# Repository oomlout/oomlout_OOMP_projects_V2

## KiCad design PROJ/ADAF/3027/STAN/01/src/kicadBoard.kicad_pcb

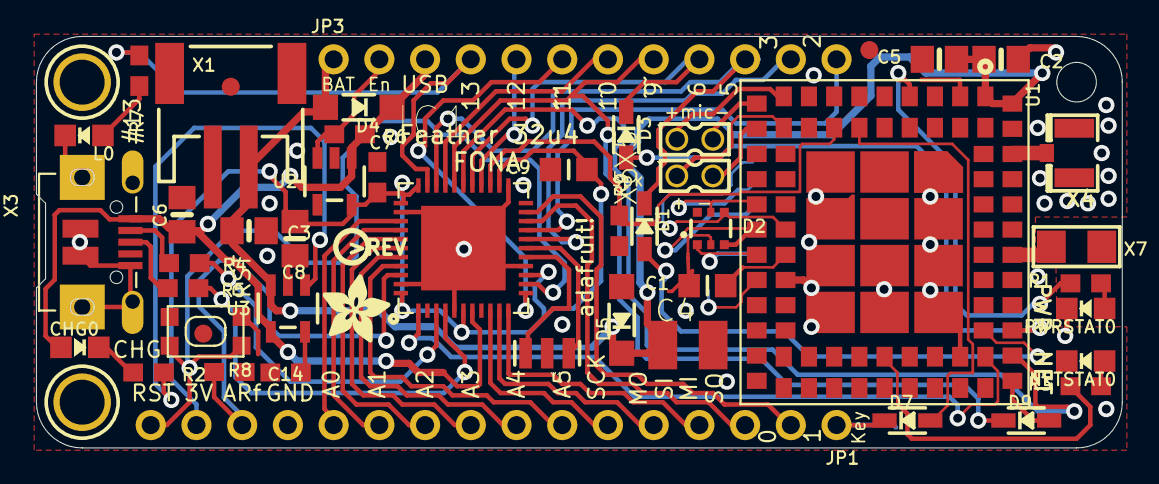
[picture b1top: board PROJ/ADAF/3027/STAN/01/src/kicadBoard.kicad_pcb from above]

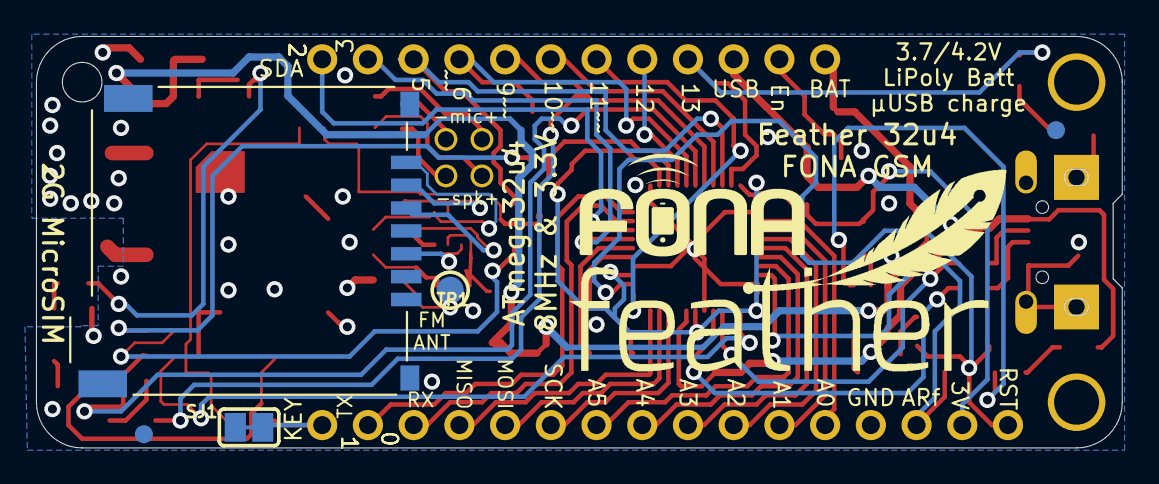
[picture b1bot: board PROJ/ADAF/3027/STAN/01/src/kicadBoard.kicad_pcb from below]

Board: 2 copper layers, 60.3 x 22.9 mm, 59 parts (7 on the bottom side), 61 nets.

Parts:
@HOLE0: (no value)
C1, C9: 10uF; _0805MP
C2: 33pF; 0805-NO
C3, C6, C8: 10µF; 0805-NO
C4: 100uF; C1210
C5: 10pF; 0805-NO
C7, C14: 1uF; 0603-NO
CHG0: ORANGE; CHIPLED_0805_NOOUTLINE
D1, D3, D7, D9: 1N4148; SOD-323
D2: SMF05C; SOT363
D4: MBR120; SOD-123
D5: MMSZ5231BT1G; SOD-123
IC1: ATMEGA32U4-MU; TQFN44_7MM
JP1: 1X16_ROUND
JP3: 1X12_ROUND
L0: RED; CHIPLED_0805_NOOUTLINE
NETSTAT0: BLUE; CHIPLED_0805_NOOUTLINE
PWRSTAT0: GREEN; CHIPLED_0805_NOOUTLINE
R1, R2, R3: 1K; 0603-NO
R4, R5: 22; 0603-NO
R6: 100k; 0603-NO
R7, R8: 2.2K; 0603-NO
R9: DNP; 0603-NO
SJ1: SOLDERJUMPER_CLOSEDWIRE
SW1: SPST_TACT-KMR2; KMR2
TP1: TESTPOINT_ROUND_1.5MM
U1: SIM800H/L; SIM800L
U2: AP2112-3.3K; SOT23-5
U3: MCP73831T-2ACI/OT; SOT23-5
U$7: ADAFRUIT_3.5MM
U$18, U$23, U$34, U$35, U$42: FIDUCIAL""; FIDUCIAL_1MM
U$25: FEATHERLOGO
U$31, U$32: MOUNTINGHOLE2.5; MOUNTINGHOLE_2.5_PLATED
U$43: FONA_LOGO_SMALL
U$44: PCBFEAT-REV-040
X1: JSTPH; JSTPH2
X2: 4UCON 20217; 4UCONN_20217
X3: microUSB; 4UCONN_20329_V2
X4: uFL; U.FL
X5, X6: 1x2; 87758-0216
X7: ANT_2450AT18B100
Y1: 8MHz; RESONATOR-SMD

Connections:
0: IC1.20, JP1.3
1: IC1.21, JP1.2
1.8V: D2.1, U1.16, X2.VCC
2: IC1.19, JP3.12
3: IC1.18, JP3.11
4_RST: IC1.25, R9.2, U1.49
5_UART_DTR: D1.C, IC1.31, JP3.10
6_UART_RTS: D3.C, IC1.27, JP3.9
7_UART_RI: IC1.1, U1.68
8_UART_TXD: IC1.28, U1.32
9_UART_RXD: D9.C, IC1.29, JP3.8
10: IC1.30, JP3.7
11: IC1.12, JP3.6
12: IC1.26, JP3.5
13: IC1.32, JP3.4, R7.1
+3V3: C7.1, C8.1, C9.1, IC1.6, IC1.14, IC1.24, IC1.33, IC1.34, IC1.44, JP1.15, U2.5
A0: IC1.36, JP1.12
A1: IC1.37, JP1.11
A2: IC1.38, JP1.10
A3: IC1.39, JP1.9
A4: IC1.40, JP1.8
A5: IC1.41, JP1.7
AREF: C14.1, IC1.42, JP1.14
D+: IC1.4, R5.2
D-: IC1.3, R4.2
EN: JP3.2, R6.1, U2.3
FM_ANT: TP1.P$1, U1.17
GND: C1.2, C2.2, C3.2, C4.2, C5.2, C6.2, C7.2, C8.2, C9.2, C14.2, D2.2, D5.A, IC1.5, IC1.15, IC1.23, IC1.35, IC1.43, JP1.13, L0.C, NETSTAT0.C, PWRSTAT0.C, R8.2, R9.1, SJ1.1, SW1.2, SW1.4, U1.2, U1.6, U1.8, U1.35, U1.37, U1.38, U1.39, U1.41, U1.43, U1.44, U1.45, U1.57, U1.58, U1.67, U1.71, U1.72, U1.73, U1.76, U1.77, U1.78, U1.79, U1.80, U1.81, U1.82, U1.83, U1.84, U1.85, U1.86, U1.87, U1.88, U2.2, U3.2, X1.1, X2.GND, X2.GND@1, X2.GND@2, X2.GND@3, X2.GND@4, X3.BASE@1, X3.BASE@2, X3.GND, X3.SPRT@1, X3.SPRT@2, X3.SPRT@3, X3.SPRT@4, X4.1, X4.2, Y1.2
GSM_ANT: U1.40, X4.3
KEY: D7.C, JP1.1, SJ1.2
MIC2+: U1.9, X5.1
MIC2-: U1.10, X5.2
MISO: IC1.11, JP1.4
MOSI: IC1.10, JP1.5
unnamed: CHG0.C, R2.1
unnamed: L0.A, R7.2
unnamed: R2.2, U3.1
unnamed: R8.1, U3.5
unnamed: PWRSTAT0.A, R1.1
unnamed: U1.36, X7.FP
unnamed: D7.A, U1.48
unnamed: NETSTAT0.A, R3.1
unnamed: IC1.16, Y1.3
unnamed: IC1.17, Y1.1
unnamed: R5.1, X3.D+
unnamed: R4.1, X3.D-
NETSTAT: R3.2, U1.64
PWRSTAT: R1.2, U1.4
RST: IC1.13, JP1.16, SW1.1, SW1.3
SCK: IC1.9, JP1.6
SIMCLK: D2.4, U1.55, X2.CLK
SIMDATA: D2.5, U1.14, X2.I/O
SIMRST: D2.3, U1.15, X2.RST
SPEAKER2+: U1.51, X6.1
SPEAKER2-: U1.11, X6.2
UART_DTR: D1.A, U1.69
UART_RTS: D3.A, U1.33
UART_RXD: D9.A, U1.31
VBAT: C2.1, C3.1, C4.1, C5.1, D4.A, D5.C, JP3.1, U1.1, U1.42, U3.3, X1.2
VBUS: C6.1, CHG0.A, D4.C, IC1.7, JP3.3, R6.2, U1.7, U2.1, U3.4, X3.VBUS
VRTC: C1.1, U1.56

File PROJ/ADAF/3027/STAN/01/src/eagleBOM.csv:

"Part";"Value";"Device";"Package";"Description";"BOM";"MF";"MPN";"OC_FARNELL";"OC_NEWARK";
"C1";"10uF";"CAP_CERAMIC_0805MP";"_0805MP";"Ceramic Capacitors";"";"";"";"";"";
"C2";"33pF";"CAP_CERAMIC0805-NOOUTLINE";"0805-NO";"Ceramic Capacitors";"";"";"";"";"";
"C3";"10µF";"CAP_CERAMIC0805-NOOUTLINE";"0805-NO";"Ceramic Capacitors";"";"";"";"";"";
"C4";"100uF";"C-USC1210";"C1210";"CAPACITOR, American symbol";"";"";"";"";"";
"C5";"10pF";"CAP_CERAMIC0805-NOOUTLINE";"0805-NO";"Ceramic Capacitors";"";"";"";"";"";
"C6";"10µF";"CAP_CERAMIC0805-NOOUTLINE";"0805-NO";"Ceramic Capacitors";"";"";"";"";"";
"C7";"1uF";"CAP_CERAMIC0603_NO";"0603-NO";"Ceramic Capacitors";"";"";"";"";"";
"C8";"10µF";"CAP_CERAMIC0805-NOOUTLINE";"0805-NO";"Ceramic Capacitors";"";"";"";"";"";
"C9";"10uF";"CAP_CERAMIC_0805MP";"_0805MP";"Ceramic Capacitors";"";"";"";"";"";
"C14";"1uF";"CAP_CERAMIC0603_NO";"0603-NO";"Ceramic Capacitors";"";"";"";"";"";
"CHG";"ORANGE";"LED0805_NOOUTLINE";"CHIPLED_0805_NOOUTLINE";"LED";"";"";"";"";"";
"D1";"1N4148";"DIODESOD-323";"SOD-323";"Diode";"";"";"";"";"";
"D2";"SMF05C";"TVSARRAY_5LANE";"SOT363";"Voltage Transient Suppressor Array";"";"";"";"";"";
"D3";"1N4148";"DIODESOD-323";"SOD-323";"Diode";"";"";"";"";"";
"D4";"MBR120";"DIODE-SCHOTTKYSOD-123";"SOD-123";"";"";"";"";"";"";
"D5";"MMSZ5231BT1G";"DIODE-ZENERSOD123";"SOD-123";"Zener Diode";"";"";"";"";"";
"D7";"1N4148";"DIODESOD-323";"SOD-323";"Diode";"";"";"";"";"";
"D9";"1N4148";"DIODESOD-323";"SOD-323";"Diode";"";"";"";"";"";
"IC1";"ATMEGA32U4-MU";"ATMEGA32U4-MU";"TQFN44_7MM";"http://www.ladyada.net/library/eagle";"";"";"";"";"";
"JP1";"";"HEADER-1X16ROUND";"1X16_ROUND";"PIN HEADER";"";"";"";"";"";
"JP3";"";"HEADER-1X12";"1X12_ROUND";"";"";"";"";"";"";
"L";"RED";"LED0805_NOOUTLINE";"CHIPLED_0805_NOOUTLINE";"LED";"";"";"";"";"";
"NETSTAT";"BLUE";"LED0805_NOOUTLINE";"CHIPLED_0805_NOOUTLINE";"LED";"";"";"";"";"";
"PWRSTAT";"GREEN";"LED0805_NOOUTLINE";"CHIPLED_0805_NOOUTLINE";"LED";"";"";"";"";"";
"R1";"1K";"RESISTOR_0603_NOOUT";"0603-NO";"Resistors";"";"";"";"";"";
"R2";"1K";"RESISTOR_0603_NOOUT";"0603-NO";"Resistors";"";"";"";"";"";
"R3";"1K";"RESISTOR_0603_NOOUT";"0603-NO";"Resistors";"";"";"";"";"";
"R4";"22";"RESISTOR_0603_NOOUT";"0603-NO";"Resistors";"";"";"";"";"";
"R5";"22";"RESISTOR_0603_NOOUT";"0603-NO";"Resistors";"";"";"";"";"";
"R6";"100k";"RESISTOR_0603_NOOUT";"0603-NO";"Resistors";"";"";"";"";"";
"R7";"2.2K";"RESISTOR_0603_NOOUT";"0603-NO";"Resistors";"";"";"";"";"";
"R8";"2.2K";"RESISTOR_0603_NOOUT";"0603-NO";"Resistors";"";"";"";"";"";
"R9";"DNP";"RESISTOR_0603_NOOUT";"0603-NO";"Resistors";"";"";"";"";"";
"SJ1";"";"SOLDERJUMPER_CLOSED";"SOLDERJUMPER_CLOSEDWIRE";"Solder Jumper - Closed";"";"";"";"";"";
"SW1";"SPST_TACT-KMR2";"SPST_TACT-KMR2";"KMR2";"SMT 6mm switch, EVQQ2 series";"";"";"";"";"";
"TP1";"";"TESTPOINTROUND1.5MM";"TESTPOINT_ROUND_1.5MM";"Test Point";"";"";"";"";"";
"U$18";"FIDUCIAL""";"FIDUCIAL""";"FIDUCIAL_1MM";"Fiducial Alignment Points";"EXCLUDE";"";"";"";"";
"U$23";"FIDUCIAL""";"FIDUCIAL""";"FIDUCIAL_1MM";"Fiducial Alignment Points";"EXCLUDE";"";"";"";"";
"U$31";"MOUNTINGHOLE2.5";"MOUNTINGHOLE2.5";"MOUNTINGHOLE_2.5_PLATED";"Mounting Hole";"EXCLUDE";"";"";"";"";
"U$32";"MOUNTINGHOLE2.5";"MOUNTINGHOLE2.5";"MOUNTINGHOLE_2.5_PLATED";"Mounting Hole";"EXCLUDE";"";"";"";"";
"U$34";"FIDUCIAL""";"FIDUCIAL""";"FIDUCIAL_1MM";"Fiducial Alignment Points";"EXCLUDE";"";"";"";"";
"U$35";"FIDUCIAL""";"FIDUCIAL""";"FIDUCIAL_1MM";"Fiducial Alignment Points";"EXCLUDE";"";"";"";"";
"U$42";"FIDUCIAL""";"FIDUCIAL""";"FIDUCIAL_1MM";"Fiducial Alignment Points";"EXCLUDE";"";"";"";"";
"U1";"SIM800H/L";"GSM_SIM800L";"SIM800L";"SIM800K Quad-Band GSM/GPRS Module";"";"";"";"";"";
"U2";"AP2112-3.3K";"VREG_SOT23-5";"SOT23-5";"SOT23-5 Fixed Voltage Regulators";"";"";"";"";"";
"U3";"MCP73831T-2ACI/OT";"MCP73831/2";"SOT23-5";"MCP73831/2 LIPO Charger";"";"";"";"";"";
"X1";"JSTPH";"CON_JST_PH_2PIN";"JSTPH2";"JST 2-Pin Right-Angle Connector";"";"";"";"";"";
"X2";"4UCON 20217";"SIM_MICRO";"4UCONN_20217";"Micro SIM Card Holder";"";"";"";"";"";
"X3";"microUSB";"USB_MICRO_20329_V2";"4UCONN_20329_V2";"USB Connectors";"";"";"";"";"";
"X4";"uFL";"ANTENNA_U.FL";"U.FL";"U.FL Antenna Connector";"";"";"";"";"";
"X5";"1x2";"87758-0216";"87758-0216";"2 Pin - 2mm Dual Row Single Wafer, Vertical T/H HDR";"";"";"87758-0216";"unknown";"94M1513";
"X6";"1x2";"87758-0216";"87758-0216";"2 Pin - 2mm Dual Row Single Wafer, Vertical T/H HDR";"";"";"87758-0216";"unknown";"94M1513";
"X7";"ANT_2450AT18B100";"ANTENNA_JOHANSON_2450AT18B100";"ANT_2450AT18B100";"Johanson 2.4GHz Chip Antenna (1206 Package)";"";"";"";"";"";
"Y1";"8MHz";"RESONATORSMD";"RESONATOR-SMD";"Resonator";"";"";"";"";"";

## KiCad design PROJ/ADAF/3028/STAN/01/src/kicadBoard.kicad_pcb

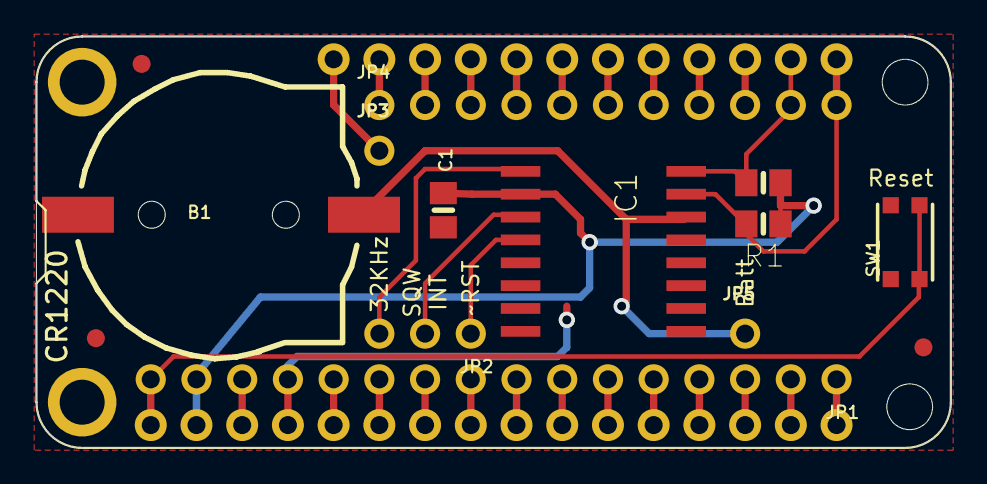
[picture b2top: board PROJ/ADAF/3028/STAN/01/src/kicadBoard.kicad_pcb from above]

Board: 16 copper layers, 50.8 x 22.9 mm, 16 parts (1 on the bottom side), 32 nets.

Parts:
B1: CR1220; CR1220-2
C1: 1uF; 0805-NO
FID1, FID2, FID3: FIDUCIAL""; FIDUCIAL_1MM
IC1: DS3231/SO; SO16W
JP1: 1X16_ROUND
JP2: 1X03_ROUND
JP3, JP5: 1X01_ROUND
JP4: 1X11_ROUND
MS1: MICROSHIELD_NODIM; MICROSHIELD_DIM
R1, R2: 10K; 0805-NO
SW1: KMR2; BTN_KMR2_4.6X2.8
U$6: FEATHERLOGO

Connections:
3.3V: C1.2, IC1.2, JP1.15, MS1.2, R1.1, R2.1
32KHZ: IC1.1, JP2.3
CR1220: B1.+, IC1.14, JP5.1
GND: B1.-, C1.1, IC1.13, JP1.13, MS1.4, SW1.A, SW1.A'
unnamed: JP1.1, MS1.16
unnamed: JP1.2, MS1.15
unnamed: JP1.3, MS1.14
unnamed: JP1.4, MS1.13
unnamed: JP1.5, MS1.12
unnamed: JP1.6, MS1.11
unnamed: JP1.7, MS1.10
unnamed: JP1.8, MS1.9
unnamed: JP1.9, MS1.8
unnamed: JP1.10, MS1.7
unnamed: JP1.11, MS1.6
unnamed: JP1.12, MS1.5
unnamed: JP4.1, MS1.27
unnamed: JP4.3, MS1.25
unnamed: JP4.4, MS1.24
unnamed: JP4.5, MS1.23
unnamed: JP4.6, MS1.22
unnamed: JP4.7, MS1.21
unnamed: JP4.8, MS1.20
unnamed: JP4.9, MS1.19
unnamed: JP1.14, MS1.3
unnamed: JP1.16, MS1.1, SW1.B, SW1.B'
SCL: IC1.16, JP4.10, MS1.18, R2.2
SDA: IC1.15, JP4.11, MS1.17, R1.2
SQW: IC1.3, JP2.2
USB: JP4.2, MS1.26
VBAT: JP3.1, MS1.28
~RTC_RST: IC1.4, JP2.1

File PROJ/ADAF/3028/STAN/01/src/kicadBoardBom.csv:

"Id";"Designator";"Package";"Quantity";"Designation";"Supplier and ref";
1;"SW1";"BTN_KMR2_4.6X2.8";1;"KMR2";;;
2;"FID1,FID3,FID2";"FIDUCIAL_1MM";3;"FIDUCIAL""";;;
3;"JP1";"1X16_ROUND";1;"";;;
4;"JP4";"1X11_ROUND";1;"";;;
5;"IC1";"SO16W";1;"DS3231/SO";;;
6;"JP3,JP5";"1X01_ROUND";2;"";;;
7;"R2,R1";"0805-NO";2;"10K";;;
8;"MS1";"MICROSHIELD_DIM";1;"MICROSHIELD_NODIM";;;
9;"C1";"0805-NO";1;"1uF";;;
10;"B1";"CR1220-2";1;"CR1220";;;
11;"JP2";"1X03_ROUND";1;"";;;
12;"U$6";"FEATHERLOGO";1;"";;;

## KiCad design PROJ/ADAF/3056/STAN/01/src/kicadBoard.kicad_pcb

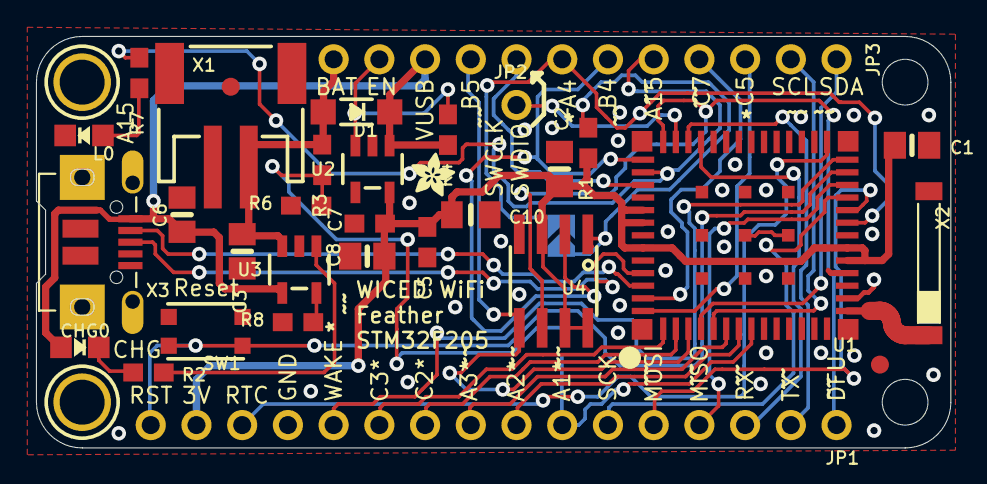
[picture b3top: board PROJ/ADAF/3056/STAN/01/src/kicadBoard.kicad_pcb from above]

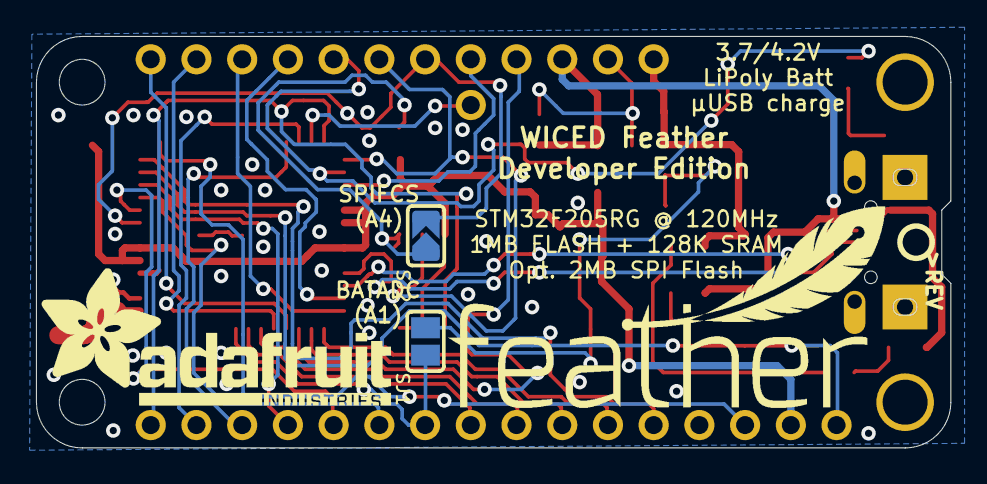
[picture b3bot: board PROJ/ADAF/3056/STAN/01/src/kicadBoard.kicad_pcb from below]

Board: 2 copper layers, 50.8 x 22.9 mm, 41 parts (5 on the bottom side), 38 nets.

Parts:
@HOLE0, @HOLE1: (no value)
C1, C2, C3, C6, C8: 10µF; 0805-NO
C5, C7: 1uF; 0603-NO
C10: 0.1uF; 0805_10MGAP
CHG0: ORANGE; CHIPLED_0805_NOOUTLINE
D1: MBR120; SOD-123
JP1: 1X16_ROUND
JP2: 1X01_ROUND
JP3: 1X12_ROUND
L0: RED; CHIPLED_0805_NOOUTLINE
R1, R4, R6: 100K; 0603-NO
R2: 1K; 0603-NO
R3: 100k; 0603-NO
R7: 2.2K; 0603-NO
R8: 4.7K; 0603-NO
SJ1: BAT; SOLDERJUMPER_REFLOW_NOPASTE
SJ2: SOLDERJUMPER_ARROW_NOPASTE
SW1: BTN_KMR2_4.6X2.8
U1: USI_WM-N-BM-09
U2: AP2112(3.3V); SOT23-5
U3: MCP73831T-2ACI/OT; SOT23-5
U4: S25FL216K; SOIC8_150MIL
U$7: FEATHERLOGO
U$8: ADAFRUIT_2.5MM
U$10: ADAFRUIT_TEXT_20MM
U$23: PCBFEAT-REV-040
U$31, U$32: MOUNTINGHOLE2.5; MOUNTINGHOLE_2.5_PLATED
U$34, U$35: FIDUCIAL""; FIDUCIAL_1MM
X1: JSTPH; JSTPH2
X2: 2500AT44M0400; ANT_2500AT44M0400
X3: 20329; 4UCONN_20329_V2

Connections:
+3V3: C1.1, C2.1, C5.1, C7.1, C8.1, C10.1, JP1.15, R1.2, U1.19, U1.20, U1.46, U1.47, U1.49, U2.5, U4.3, U4.7, U4.8
A0/WAKEUP: JP1.12, U1.27
A1/ADC1: JP1.7, SJ1.1, U1.8
A2/ADC2: JP1.8, U1.7
A3/ADC3: JP1.9, U1.6
A4/CS: JP3.6, SJ2.2, U1.22
A5/SCK1: JP1.6, U1.24
A6/MISO1: JP1.4, U1.25
A7/MOSI1: JP1.5, U1.23
A9/TXD: JP1.2, U1.39
A10/RXD: JP1.3, U1.38
A15: JP3.8, R7.1, U1.43
ANT: U1.15, X2.FEED
B4/MISO3: JP3.7, U1.42, U4.2
B5/MOSI3: JP3.4, U1.3, U4.5
B6/SCL: JP3.11, U1.5
B7/SDA: JP3.12, U1.4
C2/ADC12: JP1.10, U1.2
C3/ADC13: JP1.11, U1.1
C5: JP3.10, U1.54
C7: JP3.9, U1.53
D+: U1.51, X3.D+
D-: U1.52, X3.D-
DFU/SCK3: JP1.1, U1.41, U4.6
EN: JP3.2, R4.1, U2.3
GND: C1.2, C2.2, C3.2, C5.2, C6.2, C7.2, C8.2, C10.2, JP1.13, L0.C, R6.2, R8.2, SW1.B, SW1.B', U1.14, U1.16, U1.17, U1.18, U1.21, U1.29, U1.30, U1.37, U1.45, U1.48, U1.50, U1.55, U1.56, U1.57, U1.58, U1.59, U1.60, U1.61, U1.62, U1.63, U1.64, U1.65, U1.66, U1.67, U2.2, U3.2, U4.4, X1.1, X3.BASE@1, X3.BASE@2, X3.GND, X3.SPRT@1, X3.SPRT@2, X3.SPRT@3, X3.SPRT@4
unnamed: CHG0.C, R2.1
unnamed: L0.A, R7.2
unnamed: R2.2, U3.1
unnamed: R8.1, U3.5
unnamed: R3.2, R6.1, SJ1.2
unnamed: R1.1, SJ2.1, U4.1
SWCLK: JP2.1, U1.40
SWDIO: JP3.5, U1.44
VBAT: C3.1, D1.A, JP3.1, R3.1, U3.3, X1.2
VBUS: C6.1, CHG0.A, D1.C, JP3.3, R4.2, U2.1, U3.4, X3.VBUS
VRTC: JP1.14, U1.28
~RESET: JP1.16, SW1.A, SW1.A', U1.26

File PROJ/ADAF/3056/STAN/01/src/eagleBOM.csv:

"Part";"Value";"Device";"Package";"Description";"BOM";
"C1";"10µF";"CAP_CERAMIC0805-NOOUTLINE";"0805-NO";"Ceramic Capacitors";"";
"C2";"10µF";"CAP_CERAMIC0805-NOOUTLINE";"0805-NO";"Ceramic Capacitors";"";
"C3";"10µF";"CAP_CERAMIC0805-NOOUTLINE";"0805-NO";"Ceramic Capacitors";"";
"C5";"1uF";"CAP_CERAMIC0603_NO";"0603-NO";"Ceramic Capacitors";"";
"C6";"10µF";"CAP_CERAMIC0805-NOOUTLINE";"0805-NO";"Ceramic Capacitors";"";
"C7";"1uF";"CAP_CERAMIC0603_NO";"0603-NO";"Ceramic Capacitors";"";
"C8";"10µF";"CAP_CERAMIC0805-NOOUTLINE";"0805-NO";"Ceramic Capacitors";"";
"C10";"0.1uF";"CAP_CERAMIC0805_10MGAP";"0805_10MGAP";"Ceramic Capacitors";"";
"CHG";"ORANGE";"LED0805_NOOUTLINE";"CHIPLED_0805_NOOUTLINE";"LED";"";
"D1";"MBR120";"DIODE-SCHOTTKYSOD-123";"SOD-123";"";"";
"JP1";"";"HEADER-1X16ROUND";"1X16_ROUND";"PIN HEADER";"";
"JP2";"";"HEADER-1X1ROUND";"1X01_ROUND";"PIN HEADER";"";
"JP3";"";"HEADER-1X12";"1X12_ROUND";"";"";
"L";"RED";"LED0805_NOOUTLINE";"CHIPLED_0805_NOOUTLINE";"LED";"";
"R1";"100K";"RESISTOR_0603_NOOUT";"0603-NO";"Resistors";"";
"R2";"1K";"RESISTOR_0603_NOOUT";"0603-NO";"Resistors";"";
"R3";"100k";"RESISTOR_0603_NOOUT";"0603-NO";"Resistors";"";
"R4";"100K";"RESISTOR_0603_NOOUT";"0603-NO";"Resistors";"";
"R6";"100K";"RESISTOR_0603_NOOUT";"0603-NO";"Resistors";"";
"R7";"2.2K";"RESISTOR_0603_NOOUT";"0603-NO";"Resistors";"";
"R8";"4.7K";"RESISTOR_0603_NOOUT";"0603-NO";"Resistors";"";
"SJ1";"BAT";"SOLDERJUMPERREFLOW_NOPASTE";"SOLDERJUMPER_REFLOW_NOPASTE";"SMD Solder JUMPER";"";
"SJ2";"";"SOLDERJUMPER";"SOLDERJUMPER_ARROW_NOPASTE";"SMD Solder JUMPER";"EXCLUDE";
"SW1";"";"SWITCH_TACT_SMT4.6X2.8";"BTN_KMR2_4.6X2.8";"SMT Tact Switches";"";
"U$31";"MOUNTINGHOLE2.5";"MOUNTINGHOLE2.5";"MOUNTINGHOLE_2.5_PLATED";"Mounting Hole";"EXCLUDE";
"U$32";"MOUNTINGHOLE2.5";"MOUNTINGHOLE2.5";"MOUNTINGHOLE_2.5_PLATED";"Mounting Hole";"EXCLUDE";
"U$34";"FIDUCIAL""";"FIDUCIAL""";"FIDUCIAL_1MM";"Fiducial Alignment Points";"EXCLUDE";
"U$35";"FIDUCIAL""";"FIDUCIAL""";"FIDUCIAL_1MM";"Fiducial Alignment Points";"EXCLUDE";
"U1";"";"USI_WM-N-BM-09";"USI_WM-N-BM-09";"USI WM-N-BM-09 WICED WiFi Module";"";
"U2";"AP2112(3.3V)";"VREG_SOT23-5";"SOT23-5";"SOT23-5 Fixed Voltage Regulators";"";
"U3";"MCP73831T-2ACI/OT";"MCP73831/2";"SOT23-5";"MCP73831/2 LIPO Charger";"";
"U4";"S25FL216K";"SPIFLASH_SOIC8";"SOIC8_150MIL";"SOIC8 SPI Flash";"";
"X1";"JSTPH";"CON_JST_PH_2PIN";"JSTPH2";"JST 2-Pin Right-Angle Connector";"";
"X2";"2500AT44M0400";"ANTENNA_JOHANSON_2500AT44M0400";"ANT_2500AT44M0400";"Johanson 2.3-2.7 GHz Chip Antenna";"";
"X3";"20329";"USB_MICRO_20329_V2";"4UCONN_20329_V2";"USB Connectors";"";

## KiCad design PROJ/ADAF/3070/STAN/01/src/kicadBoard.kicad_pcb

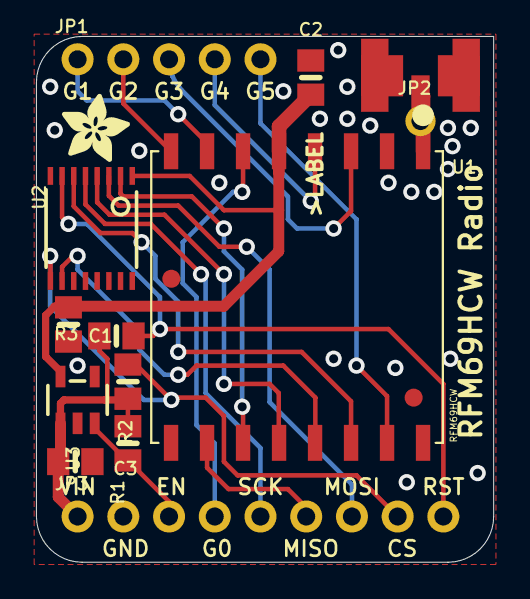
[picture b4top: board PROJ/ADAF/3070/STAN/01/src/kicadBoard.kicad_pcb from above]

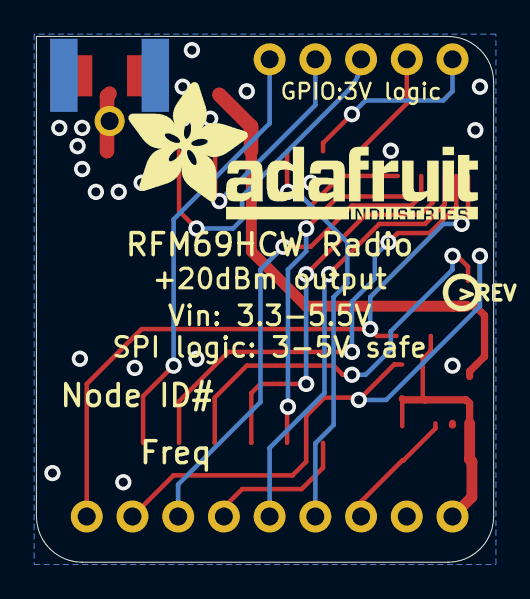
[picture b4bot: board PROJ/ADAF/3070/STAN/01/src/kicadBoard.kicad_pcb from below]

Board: 2 copper layers, 25.4 x 29.2 mm, 18 parts (2 on the bottom side), 20 nets.

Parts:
C1, C3: 10uF; 0805-NO
C2: 0.1uF; 0805-NO
FID1, FID2: FIDUCIAL""; FIDUCIAL_1MM
JP1: 1X05_ROUND_70
JP2: 1X01_ROUND
JP3: 1X09_ROUND_70
R1, R2, R3: 100K; 0805-NO
U1: RFM69HCW; RFMHCW_SMT
U2: 74HC4050D; TSSOP16
U3: AP2112K-3.3; SOT23-5
U$8: ADAFRUIT_3.5MM
U$14: PCBFEAT-REV-040
U$19: ADAFRUIT_TEXT_20MM
X1: uFL/SMA; SMA_EDGELAUNCH_UFL

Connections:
3.3V: C1.1, C2.1, U1.5P, U2.1, U3.5
CS_3V: U1.13P, U2.10
CS_5V: JP3.8, R2.1, U2.9
DIO0: JP3.4, U1.6P
DIO1: JP1.1, U1.7P
DIO2: JP1.2, U1.8P
DIO3: JP1.3, U1.3P
DIO4: JP1.4, U1.4P
DIO5: JP1.5, U1.15P
EN: JP3.3, R1.2, U3.3
GND: C1.2, C2.2, C3.2, JP3.2, U1.2P, U1.9P, U1.16P, U2.8, U3.2, X1.GND@1, X1.GND@2, X1.GND@3, X1.GND@4
MISO_3V: JP3.6, U1.10P
MOSI_3V: U1.11P, U2.2
MOSI_5V: JP3.7, U2.3
unnamed: JP2.1, U1.1P, X1.P
RST_3V: U1.14P, U2.6
RST_5V: JP3.9, R3.1, U2.7
SCK_3V: U1.12P, U2.4
SCK_5V: JP3.5, U2.5
VIN: C3.1, JP3.1, R1.1, R2.2, R3.2, U3.1

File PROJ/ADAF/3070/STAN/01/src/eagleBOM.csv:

"Part";"Value";"Device";"Package";"Description";"BOM";
"C1";"10uF";"CAP_CERAMIC0805-NOOUTLINE";"0805-NO";"Ceramic Capacitors";"";
"C2";"0.1uF";"CAP_CERAMIC0805-NOOUTLINE";"0805-NO";"Ceramic Capacitors";"";
"C3";"10uF";"CAP_CERAMIC0805-NOOUTLINE";"0805-NO";"Ceramic Capacitors";"";
"FID1";"FIDUCIAL""";"FIDUCIAL""";"FIDUCIAL_1MM";"Fiducial Alignment Points";"EXCLUDE";
"FID2";"FIDUCIAL""";"FIDUCIAL""";"FIDUCIAL_1MM";"Fiducial Alignment Points";"EXCLUDE";
"JP1";"";"HEADER-1X570MIL";"1X05_ROUND_70";"PIN HEADER";"";
"JP2";"";"HEADER-1X1ROUND";"1X01_ROUND";"PIN HEADER";"";
"JP3";"";"HEADER-1X970MIL";"1X09_ROUND_70";"PIN HEADER";"";
"R1";"100K";"RESISTOR0805_NOOUTLINE";"0805-NO";"Resistors";"";
"R2";"100K";"RESISTOR0805_NOOUTLINE";"0805-NO";"Resistors";"";
"R3";"100K";"RESISTOR0805_NOOUTLINE";"0805-NO";"Resistors";"";
"U1";"RFM69HCW";"RFM69HCW_SMT";"RFMHCW_SMT";"RFM69HCW - ISM Band RF Transceiver";"";
"U2";"74HC4050D";"74HC4050DTSSOP";"TSSOP16";"6-channel level shifter";"";
"U3";"AP2112K-3.3";"VREG_SOT23-5";"SOT23-5";"SOT23-5 Fixed Voltage Regulators";"";
"X1";"uFL/SMA";"SMACONNECTOR_EDGE_UFL";"SMA_EDGELAUNCH_UFL";"SMA Connector";"";

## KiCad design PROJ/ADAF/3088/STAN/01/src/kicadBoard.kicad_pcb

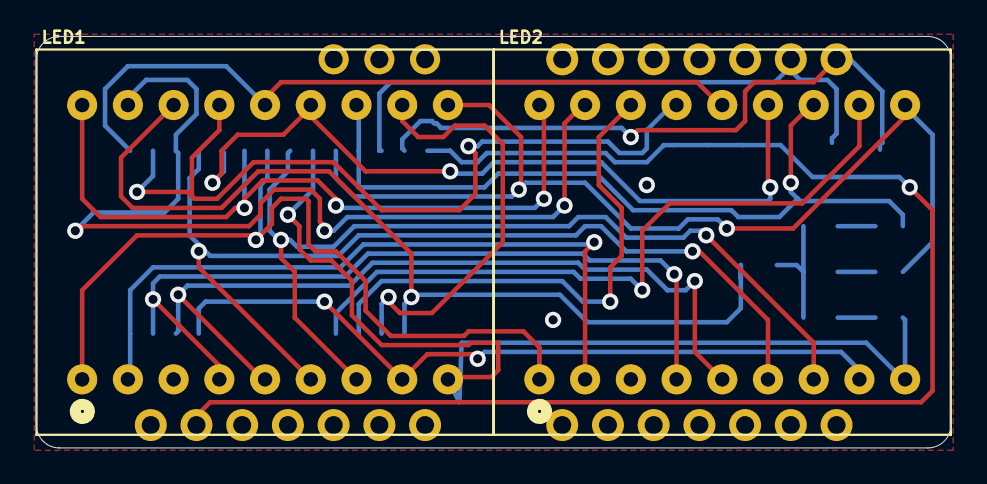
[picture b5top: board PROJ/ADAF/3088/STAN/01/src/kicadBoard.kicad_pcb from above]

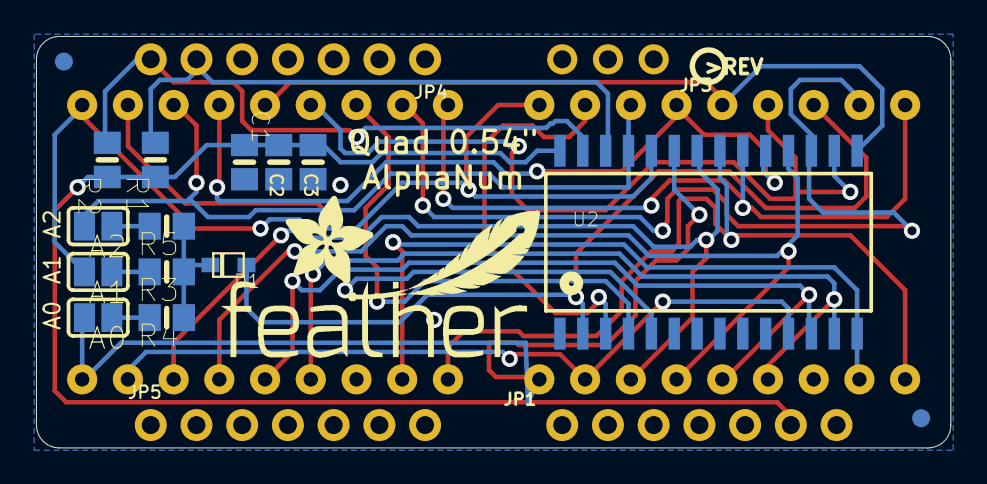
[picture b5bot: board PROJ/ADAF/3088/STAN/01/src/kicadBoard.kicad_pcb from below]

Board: 16 copper layers, 50.8 x 22.9 mm, 24 parts (22 on the bottom side), 27 nets.

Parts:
A0, A1, A2: SOLDERJUMPER_REFLOW_NOPASTE
C1, C2, C3: 10uF; 0805-NO
D1: 1N4148; SOD-323F
JP1, JP4, JP5: 1X07_ROUND_70
JP3: 1X03_ROUND
LED1, LED2: SEGMENT_STARTBUST_DUAL_KWA-541CBB
R1, R2: 10K; 0805-NO
R3, R4, R5: 47K; 0805-NO
U2: SOP28_300MIL_SKINNY
U$1, U$2: FIDUCIAL""; FIDUCIAL_1MM
U$3: PCBFEAT-REV-040
U$4: FEATHERLOGO_MED
U$5: ADAFRUIT_5MM

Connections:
A0: A0.2, LED1.9, LED2.9, U2.P$23
A1: A1.2, LED1.10, LED2.10, U2.P$24
A2: A2.2, LED1.12, LED2.12, U2.P$25
COM0: D1.A, LED1.16, U2.P$2
COM1: LED1.11, U2.P$3
COM2: LED2.16, U2.P$4
COM3: LED2.11, U2.P$5
GND: C1.2, C2.2, C3.2, JP1.4, U2.P$1
unnamed: D1.C, R3.1, R4.1, R5.1
unnamed: LED1.17, LED2.17, U2.P$17
unnamed: LED1.15, LED2.15, U2.P$16
unnamed: LED1.14, LED2.14, U2.P$15
unnamed: A2.1, R5.2
unnamed: LED1.2, LED2.2, U2.P$14
unnamed: LED1.4, LED2.4, U2.P$13
unnamed: LED1.7, LED2.7, U2.P$22
unnamed: LED1.1, LED2.1, U2.P$21
unnamed: LED1.18, LED2.18, U2.P$20
unnamed: LED1.13, LED2.13, U2.P$19
unnamed: LED1.5, LED2.5, U2.P$12
unnamed: LED1.8, LED2.8, U2.P$11
unnamed: LED1.6, LED2.6, U2.P$18
unnamed: A1.1, R3.2
unnamed: A0.1, R4.2
SCL: JP4.6, R1.2, U2.P$26
SDA: JP4.7, R2.2, U2.P$27
VDD: C1.1, C2.1, C3.1, JP1.6, R1.1, R2.1, U2.P$28

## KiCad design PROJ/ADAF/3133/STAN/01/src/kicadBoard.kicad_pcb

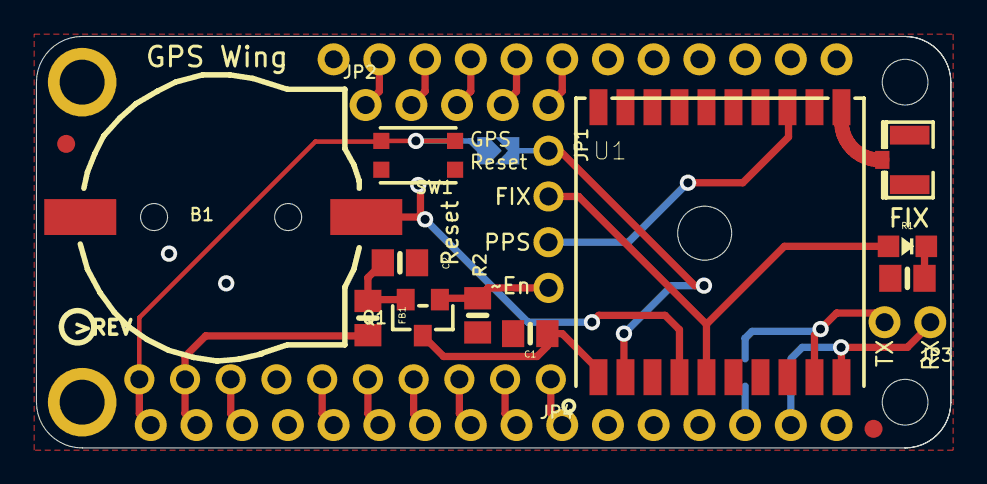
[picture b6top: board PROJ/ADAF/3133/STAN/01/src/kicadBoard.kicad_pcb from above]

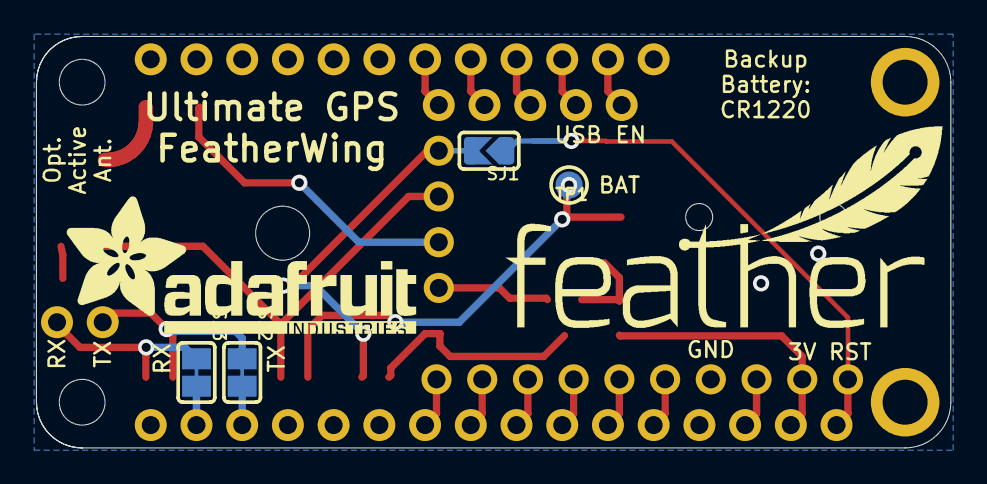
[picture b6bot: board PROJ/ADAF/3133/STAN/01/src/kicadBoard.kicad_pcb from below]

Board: 2 copper layers, 50.8 x 22.9 mm, 25 parts (6 on the bottom side), 28 nets.

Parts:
B1: CR1220; CR1220-2
C1: 0.1uF; 0805-NO
C2: 10uF; 0805-NO
FB1: Ferrite; 0805-NO
FID1, FID2: FIDUCIAL""; FIDUCIAL_1MM
JP1: 1X04_ROUND
JP2: 1X05_ROUND_70
JP3: 1X02_ROUND
JP4: 1X10_ROUND
LED1: RED; CHIPLED_0805_NOOUTLINE
MS1: FEATHERWING
Q1: DMG3415U-7; SOT23-WIDE
R1: 470 ohm; 0805-NO
R2: 100K; 0805-NO
SJ1: SOLDERJUMPER_ARROW_NOPASTE
SJ2, SJ3: SOLDERJUMPER_CLOSEDWIRE
SW1: KMR2; BTN_KMR2_4.6X2.8
TP1: TESTPOINT_ROUND_1.5MM
U1: FGPMMOPA6H
U$9: PCBFEAT-REV-040
U$10: FEATHERLOGO
U$11: ADAFRUIT_TEXT_20MM
X1: uFL; U.FL

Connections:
1PPS: JP1.3, U1.P$13
3.3V: C2.1, FB1.2, Q1.2
3V: FB1.1, JP4.9, MS1.2
ENABLE: JP1.4, Q1.1, R2.2
FIX: JP1.2, LED1.A, U1.P$5
GND: B1.-, C1.2, C2.2, JP4.7, MS1.4, R1.1, R2.1, SW1.A, SW1.A', U1.P$3, U1.P$8, U1.P$12, U1.P$19, X1.1, X1.2
GRESET: JP1.1, SJ1.2, U1.P$2
unnamed: JP2.3, MS1.25
unnamed: LED1.C, R1.2
unnamed: JP2.4, MS1.24
unnamed: U1.P$11, X1.3
unnamed: JP2.5, MS1.23
unnamed: JP4.1, MS1.10
unnamed: JP4.2, MS1.9
unnamed: JP4.3, MS1.8
unnamed: JP4.4, MS1.7
unnamed: JP4.5, MS1.6
unnamed: JP4.6, MS1.5
unnamed: JP4.10, MS1.1, SJ1.1, SW1.B, SW1.B'
unnamed: JP4.8, MS1.3
unnamed: JP2.1, MS1.27
unnamed: C1.1, Q1.3, U1.P$1
unnamed: MS1.14, SJ2.2
unnamed: MS1.15, SJ3.2
RX: JP3.1, SJ3.1, U1.P$10
TX: JP3.2, SJ2.1, U1.P$9
USB: JP2.2, MS1.26
VBACKUP: B1.+, TP1.P$1, U1.P$4

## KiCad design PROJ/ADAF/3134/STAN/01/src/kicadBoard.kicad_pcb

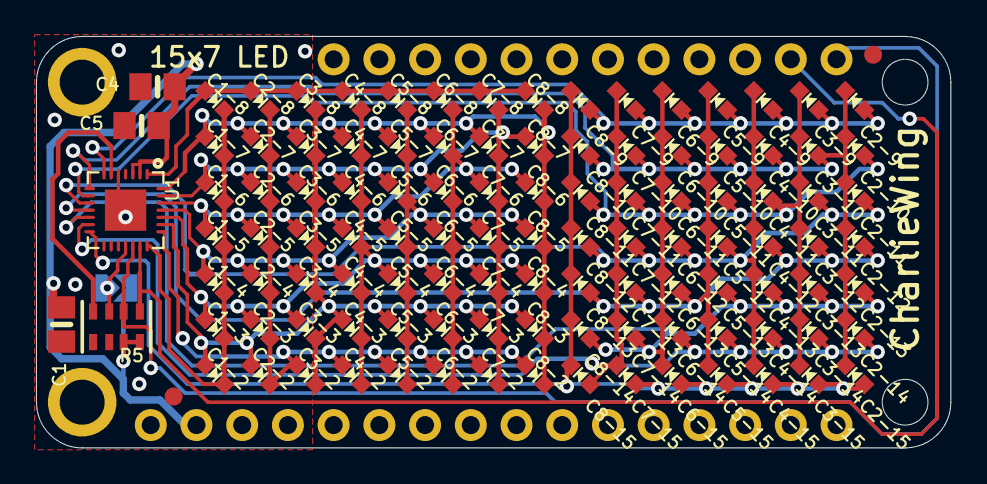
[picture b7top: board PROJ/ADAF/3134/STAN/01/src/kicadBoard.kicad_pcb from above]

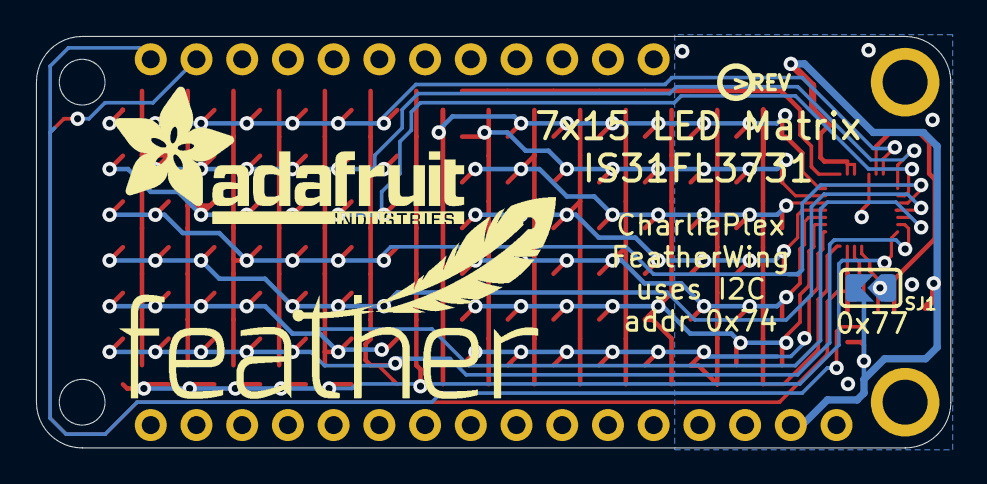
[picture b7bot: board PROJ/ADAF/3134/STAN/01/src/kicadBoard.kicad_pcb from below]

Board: 2 copper layers, 50.8 x 22.9 mm, 117 parts (4 on the bottom side), 23 nets.

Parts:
C1, C4: 10uF; 0805-NO
C1-2, C1-3, C1-4, C1-5, C1-6, C1-7, C1-8, C2-2, C2-3, C2-4, C2-5, C2-6, C2-7, C2-8, C2-9, C2-10, C2-11, C2-12, C2-13, C2-14, C2-15, C3-2, C3-3, C3-4, C3-5, C3-6, C3-7, C3-8, C3-9, C3-10, C3-11, C3-12, C3-13, C3-14, C3-15, C4-2, C4-3, C4-4, C4-5, C4-6, C4-7, C4-8, C4-9, C4-10, C4-11, C4-12, C4-13, C4-14, C4-15, C5-2, C5-3, C5-4, C5-5, C5-6, C5-7, C5-8, C5-9, C5-10, C5-11, C5-12, C5-13, C5-14, C5-15, C6-2, C6-3, C6-4, C6-5, C6-6, C6-7, C6-8, C6-9, C6-10, C6-11, C6-12, C6-13, C6-14, C6-15, C7-2, C7-3, C7-4, C7-5, C7-6, C7-7, C7-8, C7-9, C7-10, C7-11, C7-12, C7-13, C7-14, C7-15, C8-2, C8-3, C8-4, C8-5, C8-6, C8-7, C8-8, C8-9, C8-10, C8-11, C8-12, C8-13, C8-14, C8-15: CHIPLED_0603_NOOUTLINE
C5: 0.1uF; 0805-NO
FID1, FID2: FIDUCIAL""; FIDUCIAL_1MM
MS1: FEATHERWING
R5: 10K; RESPACK_4X0603
SJ1: SOLDERJUMPER_ARROW_NOPASTE
U1: IS31FL3731-SALS2; QFN28_4MM_0.4MM
U$1: PCBFEAT-REV-040
U$2: ADAFRUIT_TEXT_20MM
U$6: FEATHERLOGO

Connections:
ADDR: R5.3, SJ1.1, U1.18
CA1: C1-2.C, C1-3.C, C1-4.C, C1-5.C, C1-6.C, C1-7.C, C1-8.C, U1.21
CA2: C2-2.C, C2-3.C, C2-4.C, C2-5.C, C2-6.C, C2-7.C, C2-8.C, C3-2.A, C4-2.A, C5-2.A, C6-2.A, C7-2.A, C8-2.A, U1.22
CA3: C1-2.A, C2-2.A, C3-2.C, C3-3.C, C3-4.C, C3-5.C, C3-6.C, C3-7.C, C3-8.C, C4-3.A, C5-3.A, C6-3.A, C7-3.A, C8-3.A, U1.23
CA4: C1-3.A, C2-3.A, C3-3.A, C4-2.C, C4-3.C, C4-4.C, C4-5.C, C4-6.C, C4-7.C, C4-8.C, C5-4.A, C6-4.A, C7-4.A, C8-4.A, U1.24
CA5: C1-4.A, C2-4.A, C3-4.A, C4-4.A, C5-2.C, C5-3.C, C5-4.C, C5-5.C, C5-6.C, C5-7.C, C5-8.C, C6-5.A, C7-5.A, C8-5.A, U1.25
CA6: C1-5.A, C2-5.A, C3-5.A, C4-5.A, C5-5.A, C6-2.C, C6-3.C, C6-4.C, C6-5.C, C6-6.C, C6-7.C, C6-8.C, C7-6.A, C8-6.A, U1.26
CA7: C1-6.A, C2-6.A, C3-6.A, C4-6.A, C5-6.A, C6-6.A, C7-2.C, C7-3.C, C7-4.C, C7-5.C, C7-6.C, C7-7.C, C7-8.C, C8-7.A, U1.27
CA8: C1-7.A, C2-7.A, C3-7.A, C4-7.A, C5-7.A, C6-7.A, C7-7.A, C8-2.C, C8-3.C, C8-4.C, C8-5.C, C8-6.C, C8-7.C, C8-8.C, U1.28
CA9: C1-8.A, C2-8.A, C3-8.A, C4-8.A, C5-8.A, C6-8.A, C7-8.A, C8-8.A, U1.1
CB1: C2-9.A, C3-9.A, C4-9.A, C5-9.A, C6-9.A, C7-9.A, C8-9.A, U1.7
CB2: C2-9.C, C2-10.C, C2-11.C, C2-12.C, C2-13.C, C2-14.C, C2-15.C, C3-10.A, C4-10.A, C5-10.A, C6-10.A, C7-10.A, C8-10.A, U1.8
CB3: C2-10.A, C3-9.C, C3-10.C, C3-11.C, C3-12.C, C3-13.C, C3-14.C, C3-15.C, C4-11.A, C5-11.A, C6-11.A, C7-11.A, C8-11.A, U1.9
CB4: C2-11.A, C3-11.A, C4-9.C, C4-10.C, C4-11.C, C4-12.C, C4-13.C, C4-14.C, C4-15.C, C5-12.A, C6-12.A, C7-12.A, C8-12.A, U1.10
CB5: C2-12.A, C3-12.A, C4-12.A, C5-9.C, C5-10.C, C5-11.C, C5-12.C, C5-13.C, C5-14.C, C5-15.C, C6-13.A, C7-13.A, C8-13.A, U1.11
CB6: C2-13.A, C3-13.A, C4-13.A, C5-13.A, C6-9.C, C6-10.C, C6-11.C, C6-12.C, C6-13.C, C6-14.C, C6-15.C, C7-14.A, C8-14.A, U1.12
CB7: C2-14.A, C3-14.A, C4-14.A, C5-14.A, C6-14.A, C7-9.C, C7-10.C, C7-11.C, C7-12.C, C7-13.C, C7-14.C, C7-15.C, C8-15.A, U1.13
CB8: C2-15.A, C3-15.A, C4-15.A, C5-15.A, C6-15.A, C7-15.A, C8-9.C, C8-10.C, C8-11.C, C8-12.C, C8-13.C, C8-14.C, C8-15.C, U1.14
GND: C1.2, C4.2, C5.2, MS1.4, R5.5, R5.6, U1.5, U1.THERMAL
R_EXT: R5.4, U1.6
SCL: MS1.18, R5.1, U1.20
SDA: MS1.17, R5.2, U1.19
VCC: C1.1, C4.1, C5.1, MS1.2, R5.7, R5.8, SJ1.2, U1.2, U1.3
